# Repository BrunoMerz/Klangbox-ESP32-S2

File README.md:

Klangbox:

 Plays MP3s from filesystem if there is motion detected
 
 Hardware: ESP32-S2   lolin_s2_mini board
           SR602      motion sensor
           MAX98357A  digital audio interface 
           SD05CRMA   LiPo charging
           Speaker    8 Ohm

GPIO Pins used:
GPIO_NUM_4:    Motion Sensor
GPIO_NUM_15:   Onboard LED (for simple debugging)
GPIO_NUM_5:    Volume Potentiometer
GPIO_NUM_9:    Batteriespannung
GPIO_NUM_7:    MAX98357A  BLK
GPIO_NUM_11:   MAX98357A  DIN
GPIO_NUM_33:   MAX98357A  LRC

Deep sleep is used while the ULP (Ultra Low Coprozessor) executes a small program written in C.
This program checks periodically the motion sensor. The motion sensor detects a movement and wakes up the main processor.

Framework is ESP-IDF. 
Arduino framework can't be used because the toolchain does not support the ulp risc processor programmed in C.

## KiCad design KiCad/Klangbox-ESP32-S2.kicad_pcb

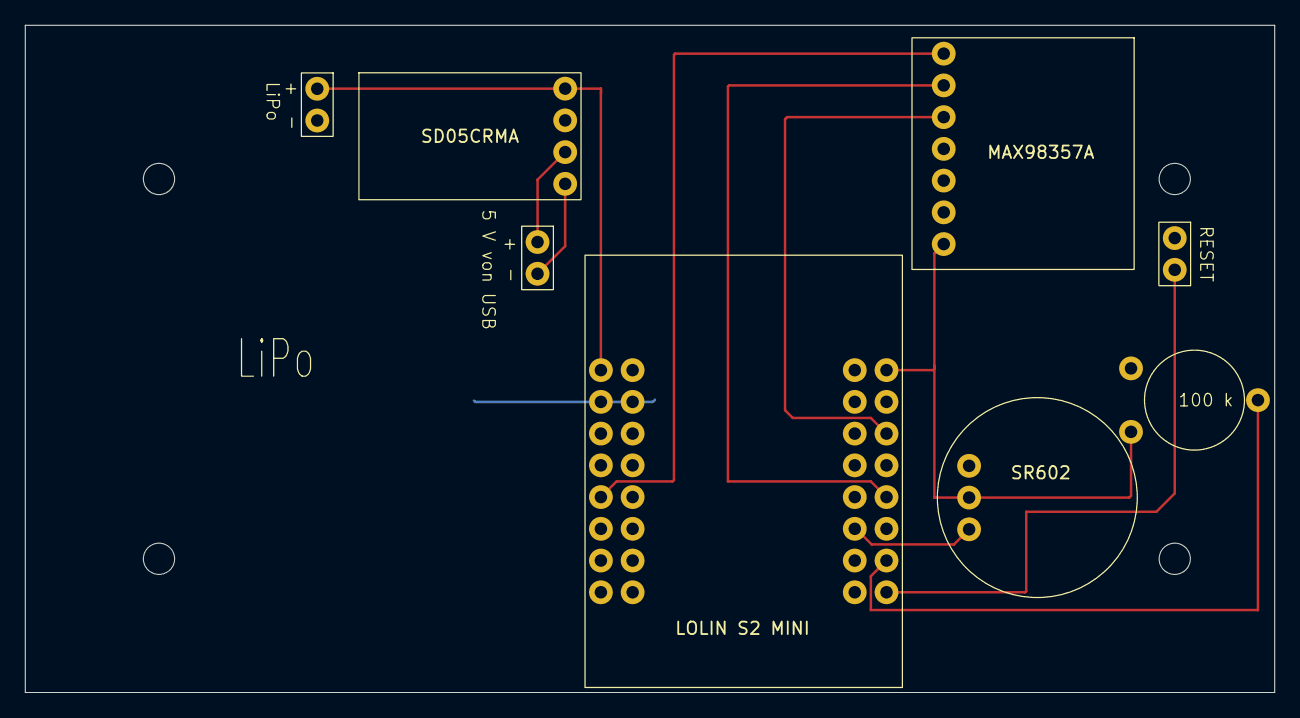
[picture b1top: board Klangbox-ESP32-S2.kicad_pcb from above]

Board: 2 copper layers, 100.0 x 53.4 mm, 8 parts (0 on the bottom side), 11 nets.

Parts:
5 V von USB: USB_C_Plug_USB2.0; USB-C
100 k: R_Potentiometer; Poti
E1: LOLIN S2 MINI; lolin_s2_mini
L1: SD05CRMA
LiPo: Battery_Cell; SW-PUSH
RESET: SW_Push; SW-PUSH
SR1: SR602
U1: MAX98357A

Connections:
+3V8: E1.31 (VBUS), L1.1 (B+), LiPo.1 (+)
GND: 100 k.1, E1.29 (GND), E1.30 (GND), L1.2 (B-), LiPo.2 (-), RESET.1, SR1.3 (-), U1.3 (GND)
unnamed: 100 k.3, E1.16 (3.3V), SR1.2 (+), U1.7 (VDD)
unnamed: 100 k.2, E1.4 (GPIO_3)
unnamed: E1.5 (GPIO_4), SR1.1 (OUT)
unnamed: E1.8 (GPIO_7), U1.16 (BCLK)
unnamed: E1.12 (GPIO_11), U1.1 (DIN)
unnamed: E1.23 (GPIO_33), U1.14 (LRCLK)
unnamed: E1.2 (~RESET), RESET.2
unnamed: 5 V von USB.A1 (GND), L1.3 (GND)
unnamed: 5 V von USB.A4 (VBUS), L1.4 (VIN)

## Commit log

2026-04-09 ESP Pins for Volume and Battery PCB design added
2026-04-24 File handling corrected Frosch.mp3 added Silouette Studio file added for plotting front cover
2026-04-30 Added play link in Klangbox file manager
2026-04-30 Not needed any more
